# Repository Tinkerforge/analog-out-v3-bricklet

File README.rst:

Analog Out Bricklet 3.0
=======================

This repository contains the firmware source code and the hardware design
files. The documentation generator configs can be found at
https://github.com/Tinkerforge/generators

Repository Content
------------------

software/:
 * examples/: Examples for all supported languages
 * build/: Compiled files
 * src/: Source code of firmware
 * Makefile: Makefile to build project

hardware/:
 * Contains KiCad project files and additionally schematics as PDF

datasheets/:
 * Contains datasheets for sensors and complex ICs that are used

Hardware
--------

The hardware is designed with the open source EDA Suite KiCad
(http://www.kicad.org). Before you are able to open the files,
you have to install the Tinkerforge kicad-libraries
(https://github.com/Tinkerforge/kicad-libraries). You can either clone
them directly in hardware/ or clone them in a separate folder and
symlink them into hardware/
(ln -s kicad_path/kicad-libraries project_path/hardware). After that you
can open the .pro file in hardware/ with KiCad and from there view and
modify the schematics and the PCB layout.

Software
--------

If you want to do your own Brick/Bricklet firmware development we highly
recommend that you use our build environment setup script and read the
tutorial (https://www.tinkerforge.com/en/doc/Tutorials/Tutorial_Build_Environment/Tutorial.html).

To compile the C code we recommend you to install the newest GNU Arm Embedded
Toolchain (https://launchpad.net/gcc-arm-embedded/+download).
You also need to install bricklib2 (https://github.com/Tinkerforge/bricklib2).

You can either clone it directly in software/src/ or clone it in a
separate folder and symlink it into software/src/
(ln -s bricklib_path/bricklib2 project_path/software/src/). Finally make sure to
have CMake installed (http://www.cmake.org/cmake/resources/software.html).

After that you can build the firmware by invoking make in software/.
The firmware (.zbin) can then be found in software/build/ and uploaded
with brickv (click button "Flashing" on start screen).

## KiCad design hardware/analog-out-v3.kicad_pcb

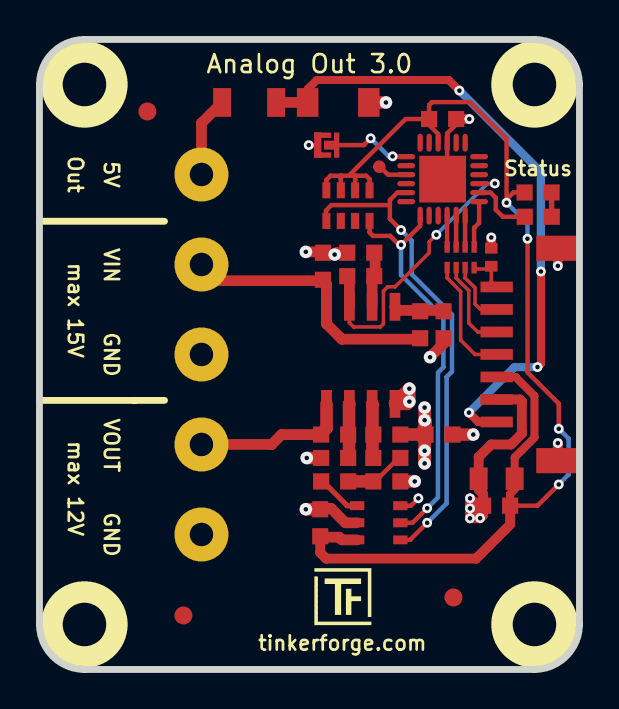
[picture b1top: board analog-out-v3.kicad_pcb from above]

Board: 2 copper layers, 30.0 x 35.0 mm, 40 parts (0 on the bottom side), 28 nets.

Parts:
C1, C2, C7: 100nF; C0603F
C3: 10uF; C0805
C4: 180pF; C0603F
C5: 220pF; C0402F
C6: 1uF; C0603F
D1: 5V; MiniMelf
D2: blue; D0603F
F1: OZCJ0035FF2G; F1206
Fiducial_Mark: VAL**; Fiducial_Mark
Fiducial_Mark#2, Fiducial_Mark#3: VAL**; Fiducial_Mark
P1: DEBUG; DEBUG_PAD
P2: CONN_5; AKL_5_5
P3: CON-SENSOR2
P4: BOOT; SolderJumper
R1: 68.1; R0603F
R2: 0; R0603F
R3, R4: 3k3; R0603F
R5, R6, R7, R8: 12k; R0603F
R9, R10: 68k; R0603F
R11: 1k; R0603F
RP1: 82; 4X0402
RP2: 2k2; 4X0603
Ref**: Val**; Logo_31x31
U1: XMC1100; QFN24-4x4mm-0.5mm
U2: MCP4725A0; SOT23-6
U3: TLV272IS; SOIC8
U4, U5, U6, U7: DRILL; DRILL_NP
VAL: CE_5mm
VAL#2: WEEE_7mm

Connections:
3V3: C2.1, C3.1, C6.1, C7.2, D2.1, P3.3, RP2.1, RP2.2, RP2.3, RP2.4, U1.10, U2.3
+5V: D1.2, F1.1, P3.1
AGND: C1.2, C2.2, C4.2, P2.1, P2.3, R2.2, R3.2, R6.2, R7.2, R9.1, U2.2, U2.6, U3.4
GND: C3.2, C5.2, C6.2, C7.1, D1.1, P3.2, P3.EP, P4.1, R2.1, U1.9, U1.EXP
unnamed: C4.1, R1.1, R4.1
unnamed: C5.1, P3.7, RP1.4
unnamed: D2.2, R11.2
unnamed: F1.2, P2.5
unnamed: P1.1, U1.15
unnamed: P2.2, R8.1, U3.1
unnamed: P3.4, RP1.1
unnamed: P3.5, RP1.2
unnamed: P3.6, RP1.3
unnamed: P4.2, U1.13
unnamed: R1.2, U2.1
unnamed: R3.1, R8.2, U3.2
unnamed: R4.2, R6.1, U3.3
unnamed: R5.1, R9.2, U3.6
unnamed: R7.1, R10.2, U3.5
unnamed: R11.1, U1.2
S-CLK: RP1.7, U1.23
S-CS: RP1.8, U1.22
S-MISO: RP1.5, U1.1
S-MOSI: RP1.6, U1.24
SCL: RP2.5, U1.19, U2.5
SDA: RP2.8, U1.17, U2.4
VCC: C1.1, P2.4, R10.1, U3.8
VIN: R5.2, U1.3, U3.7

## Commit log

2018-02-22 Add datasheet
2018-02-23 Add .gitignore
2018-03-01 Add initial schematic
2018-03-01 Add layout
2018-03-13 Add fiducials
2018-04-09 Add auto-generated stub firmware for Analog Out 3.0
2018-04-10 fix VIN routing, change LED pin
2018-04-10 Use correct pins
2018-04-10 Add configs for MCP4725 and voltage measurement
2018-04-10 Implement API
2018-04-17 Remove timeout handling (now directly done in I2CFifo)
2018-05-11 Rename files
2018-05-15 hardware: Remove special library
2018-05-23 Add some examples
2018-05-24 perl: Use strict in examples
2018-05-25 Add LabVIEW example
2018-06-06 pullup 4k7->2k2, fix origin, fix logos
2018-06-18 Change capacitor footprint(s) to C0402F
2018-06-28 Fix readme
2018-07-11 Add Makefile with docker support
2018-07-11 Remove obsolete generate_makefile scripts
2018-07-11 Update directory structure and build instructions
2018-07-17 Turn logging off
2018-07-17 specify processor
2018-07-31 Add 3d model (*.FCStd & *.step)
2018-07-31 Add PDF schematic
2018-10-02 Add BOOTLOADER_FIX_POINTER_END define
2018-10-04 Add rev to changelog
2018-10-16 Remove in-development marker
2018-11-07 rust: Accept host names for ip connection, fix naming inconsistencies
2018-12-14 Add go examples.
2018-12-18 go: Change import path.
2018-12-18 go: Change import path again.
2018-12-20 rust: Reformat examples.
2019-01-24 mqtt: Add examples.
2019-01-24 mqtt: Fix example header.
2019-01-24 mqtt: Remove executable bit in example permissions.
2019-01-24 go: Minor example fixes.
2019-05-29 Increase version for new release (changes in bricklib2)
2020-01-13 examples: Use python3 input instead of python2 raw_input.
2020-03-16 Whitespace
2020-04-07 examples: rust: Always block when calling bindings functions.
2020-08-19 Add uc examples.
2020-08-25 uc: Fix whitespace
2020-08-27 uc: Fix warnings.
2020-09-02 uc: Add example driver note.
2021-10-25 Update KiCad link
    https://www.kicad.org/blog/2021/10/Avoid-links-to-former-kicad-domain/
2022-01-05 specify processor as XMC1100
2022-04-19 examples: uc: Rename TF_HalContext to TF_HAL.
2022-04-27 uc: Adapt to bindings changes
2022-05-30 fix schematic
2022-07-06 Add license files.
2025-10-04 Fix compatibility with new Docker build image (GCC 14.2.1)

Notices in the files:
hardware/analog-out-v3.kicad_pcb:
Licensed under CERN OHL v.1.1
Copyright (©) 2018, L.Lauer
Copyright Tinkerforge GmbH 2015.
This documentation describes Open Hardware and is licensed under the
CERN OHL v. 1.1.
